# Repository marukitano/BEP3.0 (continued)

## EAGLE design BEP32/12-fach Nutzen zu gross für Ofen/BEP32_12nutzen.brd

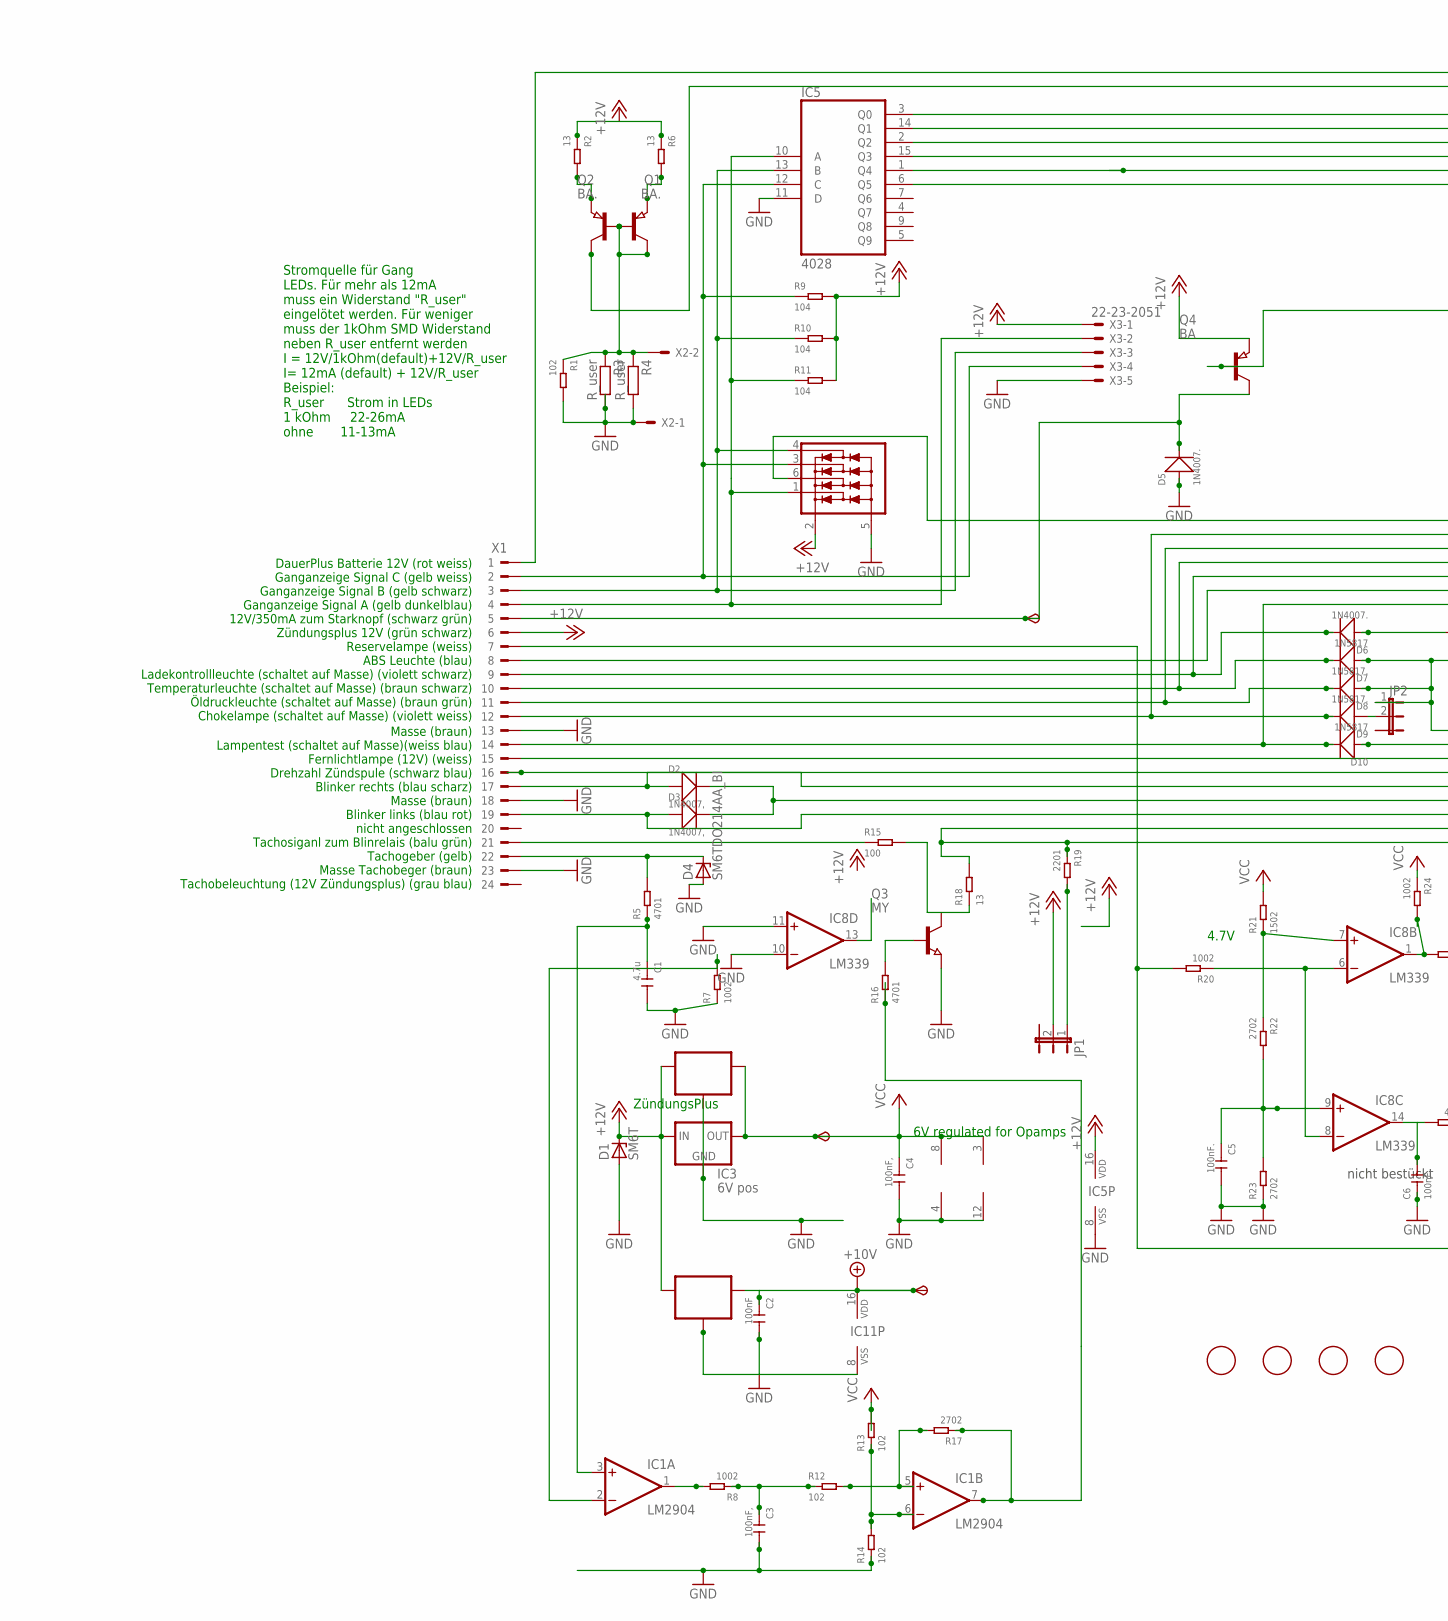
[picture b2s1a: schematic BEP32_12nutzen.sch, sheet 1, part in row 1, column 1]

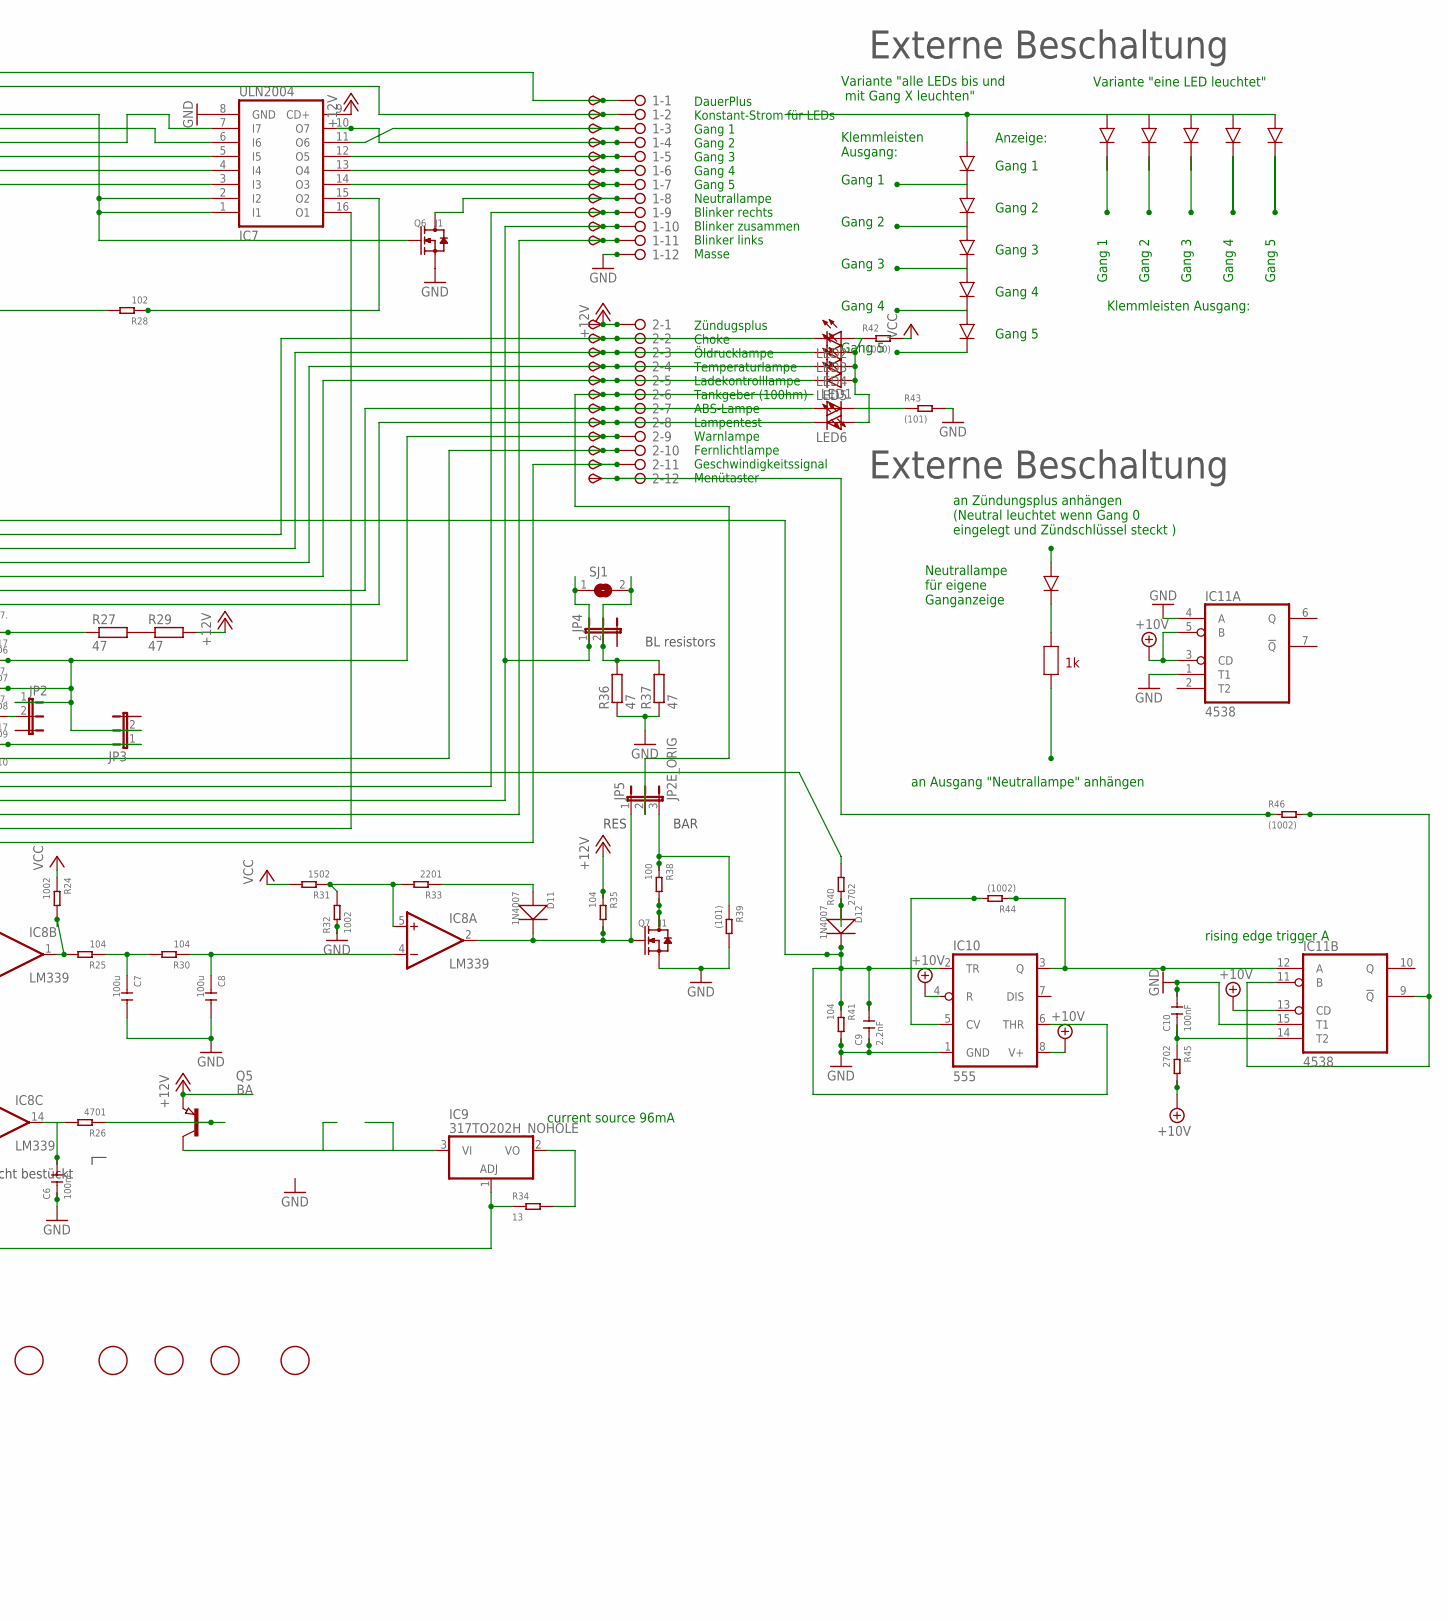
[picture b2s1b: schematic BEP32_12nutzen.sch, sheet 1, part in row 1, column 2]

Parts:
1, 2: 2081-1132; 12-PIN
6V, 10V: TPSB2.0; B2.0
C1: 4.7u; C0805
C2, C10: 100nF; C0805
C3, C4: 100nF,; C0805
C5, C6: 100nF.; C0805
C7, C8: 100u; C1206
C9: 2.2nF; C0805
D1: SM6T; DO214AA
D2, D3: 1N4007,; DO-214AC
D4: SM6TDO214AA_BI; DO214AA_BI
D5, D6: 1N4007.; DO-214AC
D7, D10: 1N5817; DO-214AC_SLIM
D8, D9: 1N5817.; DO-214AC_SLIM
D11, D12: 1N4007; DO-214AC
FID1, FID2, FID3, FID4, FID49, FID50, FID51, FID52: FIDUCIAL; FIDUCIAL_1MM
IC1: LM2904; SO08
IC2: 78L06; SOT89_ROUND
IC3: 6V pos; 78LXX
IC4: 78L10; SOT89_ROUND
IC5: 4028; SO16
IC6: NUP4304SOT457_R; SOT457R_PHILIPS
IC7: ULN2004; SO16
IC8: LM339; SO14
IC9: 317TO202H_NOHOLE; TO220H_NOHOLE
IC10: 555; SO08
IC11: 4538; SO16
JP1, JP2, JP3, JP4: JP2EJP2_SMALLPADS; JP2_SMALLPADS
JP5: JP2E_ORIG; JP2_ORIG_SMALLPADS
LED1, LED2, LED3, LED4, LED5, LED6: LEDLD260; LD260
Q1, Q2: BA.; SOT89
Q3: MY; SOT89
Q4, Q5: BA; SOT89
Q6, Q7: J1; SOT-23
R1, R12, R13, R14, R28: 102; R0805
R2, R6, R18, R34: 13; R1206
R3, R4: R_user; R0805
R5, R16, R26: 4701; R0805
R7, R8, R20, R24, R32: 1002; R0805
R9, R10, R11, R25, R30, R35, R41: 104; R0805
R15, R38: 100; R0805
R17, R22, R23, R40, R45: 2702; R0805
R19, R33: 2201; R0805
R21, R31: 1502; R0805
R27, R29, R36, R37: 47; V235/17_1MM
R39, R43: (101); R0805
R42: (1000); R0805
R44, R46: (1002); R0805
SJ1: SJ
START: TPSB2.0; B2.0
TP1, TP2, TP3, TP4, TP5, TP6, TP7, TP8, TP9, TP10, TP11, TP12, TP13, TP16, TP17, TP18, TP19, TP21, TP22, TP23, TP25, TP26: TPSB2.0; B2.0
TP24: TPSB1,27; B1,27
X1: CON_BMWV2; 24-PIN_V2
X2: 22-23-2021
X3: 22-23-2051

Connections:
+10V: 10V.TP, C2.1, IC4.1 (OUT), IC10.4 (R), IC10.8 (V+), IC11.3 (CD), IC11.5 (B), IC11.13 (CD), IC11.16 (VDD), R45.2; also elsewhere on the board
+12V: 2.1, D1.C, IC2.3 (IN), IC3.IN, IC4.3 (IN), IC5.16 (VDD), IC6.2 (V+), IC7.9 (CD+), JP1.2, Q4.3 (E), Q5.3 (E), R2.1, R6.1, R9.2, R10.2, R11.2, R29.2, R35.1, TP12.TP, X1.6, X3.1; also elsewhere on the board
+12V1: IC1.7 (OUT), R16.1, R17.1
GND: 1.12, C1.2, C2.2, C3.2, C4.2, C5.2, C6.1, C7.2, C8.2, C9.1, C10.2, D1.A, D4.A, D5.1 (+), IC1.4 (V-), IC2.2 (GND), IC2.2@1 (GND), IC3.GND, IC4.2 (GND), IC4.2@1 (GND), IC5.8 (VSS), IC5.11 (D), IC6.5 (V-), IC7.8 (GND), IC8.10 (-IN), IC8.11 (+IN), IC8.12 (GND), IC10.1 (GND), IC11.1 (T1), IC11.4 (A), IC11.8 (VSS), IC11.15 (T1), Q3.3 (E), Q6.2 (S), Q7.2 (S), R1.2, R3.2, R4.2, R7.1, R14.1, R23.1, R32.1, R36.1, R37.1, R39.2, R41.2, R43.2, X1.13, X1.18, X1.23, X2.1, X3.5; also elsewhere on the board
unnamed: 2.9, D7.1 (+), D8.1 (+), JP2.1, JP3.2, TP24.TP
unnamed: IC5.10 (A), IC6.1 (D1), R11.1, X1.4, X3.2
unnamed: IC5.13 (B), IC6.4 (D4), R10.1, X1.3, X3.3
unnamed: 2.7, LED1.A, TP22.TP, X1.8
unnamed: Q1.3 (E), R2.2
unnamed: D11.2 (-), IC8.2 (OUT), JP5.1, Q7.1 (G), R35.2
unnamed: IC1.2 (-IN), R7.2
unnamed: R27.2, R29.1
unnamed: Q2.3 (E), R6.2
unnamed: D5.2 (-), Q4.2 (C), START.TP, X1.5
unnamed: 2.2, D9.2 (-), LED2.K (C), TP16.TP, X1.12
unnamed: 2.3, D8.2 (-), LED3.K (C), TP17.TP, X1.11
unnamed: 2.4, D7.2 (-), LED4.K (C), TP18.TP, X1.10
unnamed: IC9.3 (VI), Q5.2 (C)
unnamed: IC8.6 (-IN), IC8.8 (-IN), R20.1
unnamed: IC5.12 (C), IC6.3 (D3), R9.1, X1.2, X3.4
unnamed: IC5.15 (Q3), IC7.5 (I5)
unnamed: 2.8, D10.2 (-), LED6.K (C), TP23.TP, X1.14
unnamed: 1.9, D2.1 (+), TP9.TP, X1.17
unnamed: 1.11, D3.1 (+), TP11.TP, X1.19
unnamed: IC11.9 (!Q), IC11.11 (B), R46.2
unnamed: D4.C, R5.2, X1.22
unnamed: C1.1, IC1.3 (+IN), R5.1
unnamed: 1.6, IC7.13 (O4), TP6.TP
unnamed: 1.7, IC7.14 (O3), TP7.TP
unnamed: 2.11, IC7.16 (O1), R18.2, R19.1, TP26.TP
unnamed: 2.6, JP5.2, TP21.TP
unnamed: JP1.1, R19.2
unnamed: C5.1, IC8.9 (+IN), R22.2, R23.2
unnamed: C6.2, IC8.14 (OUT), R26.2
unnamed: C9.2, D12.2 (-), IC6.6 (D2), IC10.2 (TR), IC10.6 (THR), R41.1
unnamed: LED1.K (C), R43.1
unnamed: IC9.1 (ADJ), R20.2, R34.1, X1.7
unnamed: Q5.1 (B), R26.1
unnamed: IC5.2 (Q2), IC7.7 (I7)
unnamed: 1.3, IC7.11 (O6), TP3.TP
unnamed: 1.5, IC7.12 (O5), TP5.TP
unnamed: LED2.A, LED3.A, LED4.A, LED5.A, LED6.A, R42.1
unnamed: R40.2, X1.16
unnamed: Q4.1 (B), R28.2
unnamed: IC5.3 (Q0), IC7.1 (I1), IC7.2 (I2), Q6.1 (G)
unnamed: C7.1, R25.1, R30.2
unnamed: C8.1, IC8.4 (-IN), R30.1
unnamed: IC8.5 (+IN), R31.1, R32.2, R33.2
unnamed: Q7.3 (D), R38.2
unnamed: D11.1 (+), R33.1
unnamed: IC5.1 (Q4), IC7.4 (I4)
unnamed: R15.1, X1.21
unnamed: 1.8, Q6.3 (D), TP8.TP
unnamed: 2.10, TP25.TP, X1.15
unnamed: D6.1 (+), R27.1
unnamed: 2.5, D6.2 (-), LED5.K (C), TP19.TP, X1.9
unnamed: IC5.14 (Q1), IC7.6 (I6)
unnamed: Q1.1 (B), Q2.1 (B), Q2.2 (C), R1.1, R3.1, R4.1, X2.2
unnamed: Q3.2 (C), R15.2, R18.1
unnamed: 1.2, Q1.2 (C), TP2.TP
unnamed: IC5.6 (Q5), IC7.3 (I3)
unnamed: IC9.2 (VO), R34.2
unnamed: IC10.5 (CV), R44.2
unnamed: 1.4, IC7.10 (O7), TP4.TP
unnamed: 1.1, TP1.TP, X1.1
unnamed: IC8.7 (+IN), R21.1, R22.1
unnamed: Q3.1 (B), R16.2
unnamed: IC10.3 (Q), IC11.12 (A), R44.1
unnamed: D12.1 (+), R40.1
unnamed: IC7.15 (O2), R28.1
unnamed: C10.1, IC11.14 (T2), R45.1
unnamed: 2.12, R46.1, TP13.TP
unnamed: IC1.1 (OUT), R8.2
unnamed: 1.10, D2.2 (-), D3.2 (-), JP4.1, SJ1.1, TP10.TP
unnamed: JP4.2, R36.2, R37.2, SJ1.2
unnamed: D9.1 (+), JP2.2
unnamed: C3.1, R8.1, R12.1
unnamed: IC1.5 (+IN), R12.2, R17.2
unnamed: D10.1 (+), JP3.1
unnamed: JP5.3, R38.1, R39.1
unnamed: IC1.6 (-IN), R13.1, R14.2
unnamed: IC8.1 (OUT), R24.2, R25.2
VCC: 6V.TP, C4.1, IC1.8 (V+), IC2.1 (OUT), IC3.OUT, IC8.3 (V+), R13.2, R21.2, R24.1, R31.2, R42.2; also elsewhere on the board

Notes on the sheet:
6V regulated for Opamps
current source 96mA
ZündungsPlus
Zündugsplus Choke Öldrucklampe Temperaturlampe Ladekontrolllampe Tankgeber (100hm) ABS-Lampe Lampentest Warnlampe Fernlichtlampe Geschwindigkeitssignal Menütaster
DauerPlus Konstant-Strom für LEDs Gang 1 Gang 2 Gang 3 Gang 4 Gang 5 Neutrallampe Blinker rechts Blinker zusammen Blinker links Masse
DauerPlus Batterie 12V (rot weiss) Ganganzeige Signal C (gelb weiss) Ganganzeige Signal B (gelb schwarz) Ganganzeige Signal A (gelb dunkelblau) 12V/350mA zum Starknopf (schwarz grün) Zündungsplus 12V (grün schwarz) Reservelampe (weiss) ABS Leuchte (blau) Ladekontrollleuchte (schaltet auf Masse) (vi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
Masse (braun) Lampentest (schaltet auf Masse)(weiss blau) Fernlichtlampe (12V) (weiss) Drehzahl Zündspule (schwarz blau) Blinker rechts (blau scharz) Masse (braun) Blinker links (blau rot) nicht angeschlossen Tachosiganl zum Blinrelais (balu grün) Tachogeber (gelb) Masse Tachobeger (braun) Tachobel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
4.7V
Stromquelle für Gang LEDs. Für mehr als 12mA muss ein Widerstand "R_user" eingelötet werden. Für weniger muss der 1kOhm SMD Widerstand neben R_user entfernt werden I = 12V/1kOhm(default)+12V/R_user I= 12mA (default) + 12V/R_user Beispiel: R_user Strom in LEDs 1 kOhm 22-26mA ohne 11-13mA
Gang 1
Gang 2
Gang 3
Gang 4
Gang 5
Variante "eine LED leuchtet"
Variante "alle LEDs bis und mit Gang X leuchten"
Klemmleisten Ausgang:
Klemmleisten Ausgang:
an Zündungsplus anhängen (Neutral leuchtet wenn Gang 0 eingelegt und Zündschlüssel steckt )
an Ausgang "Neutrallampe" anhängen
Neutrallampe für eigene Ganganzeige
Externe Beschaltung
Anzeige:
nicht bestückt
rising edge trigger A
BAR
RES
BL resistors

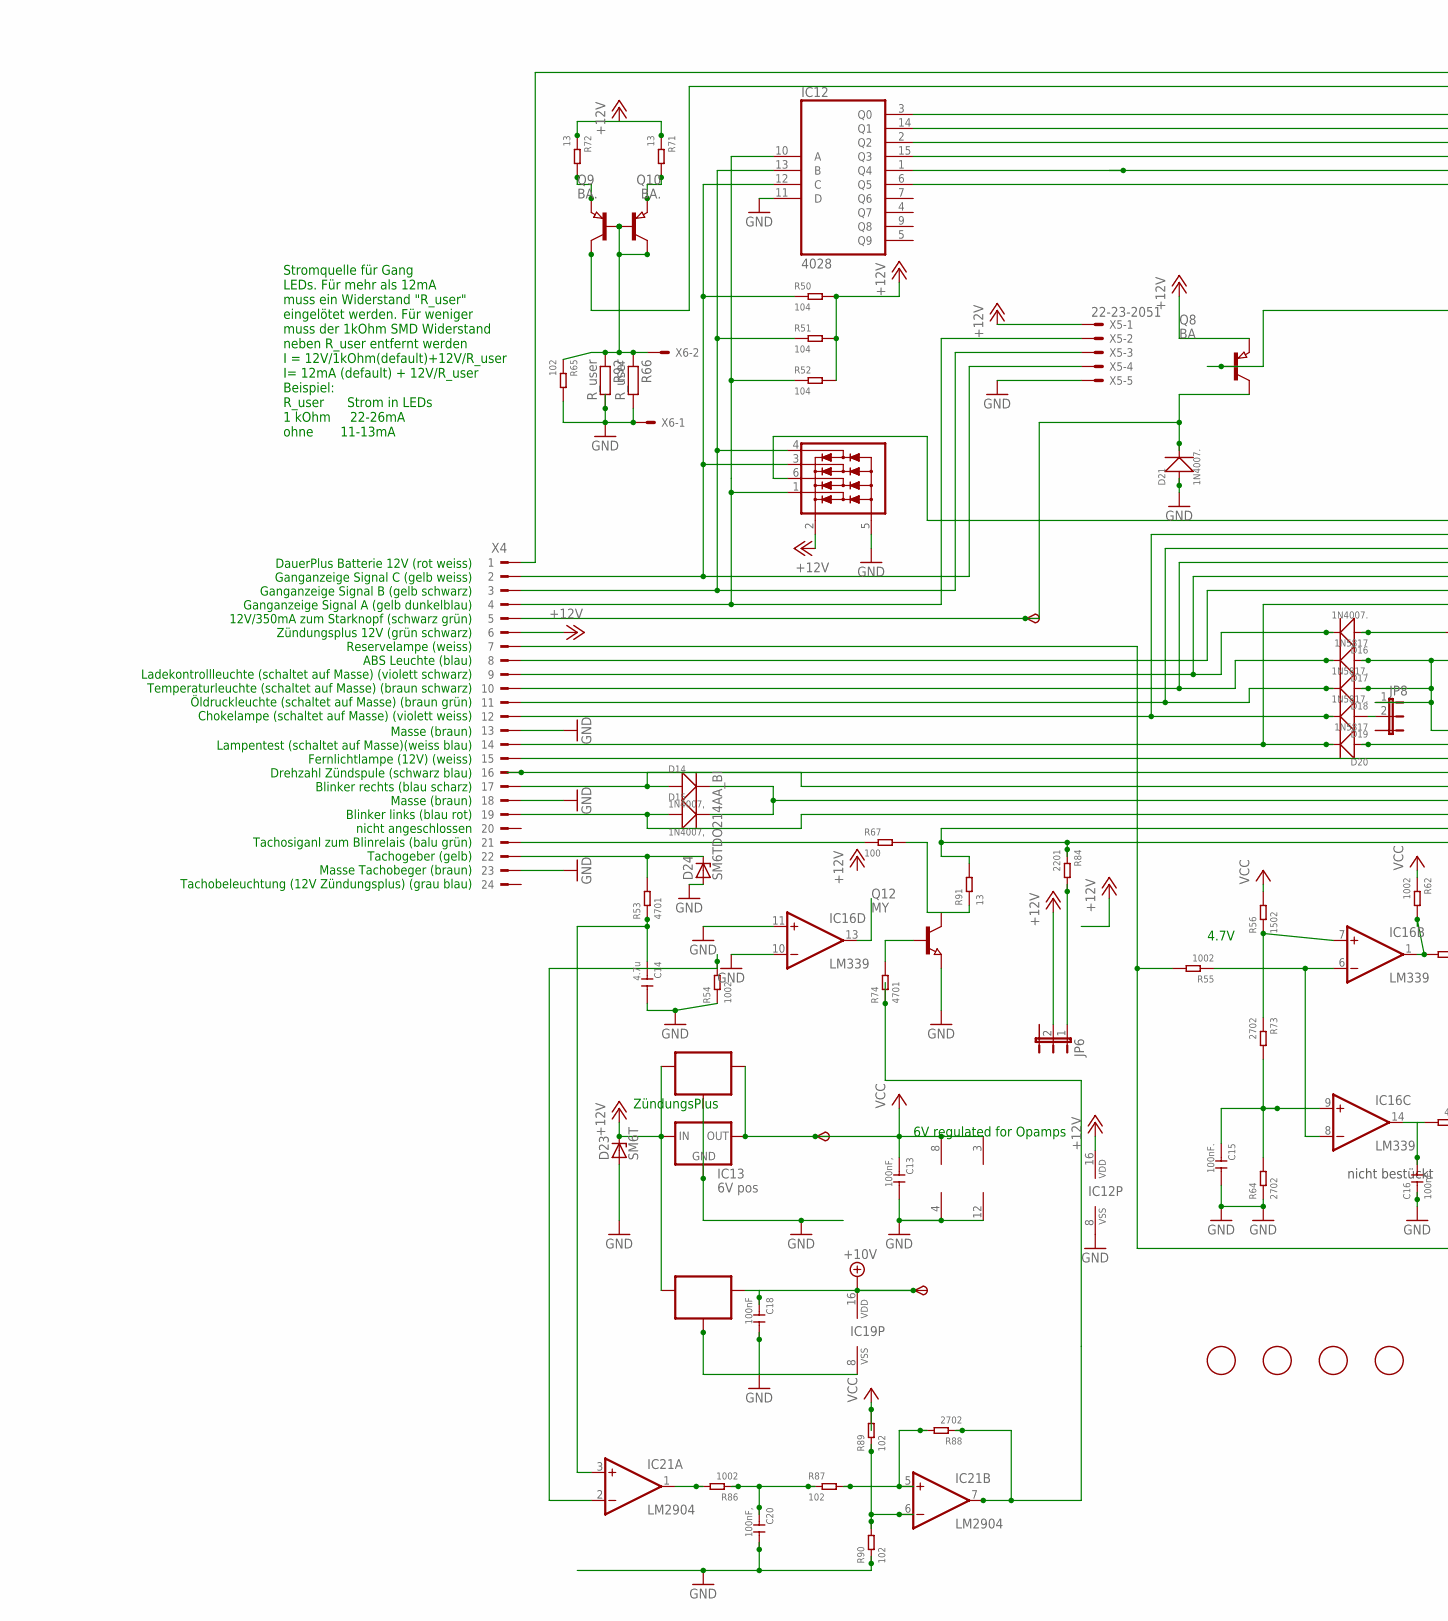
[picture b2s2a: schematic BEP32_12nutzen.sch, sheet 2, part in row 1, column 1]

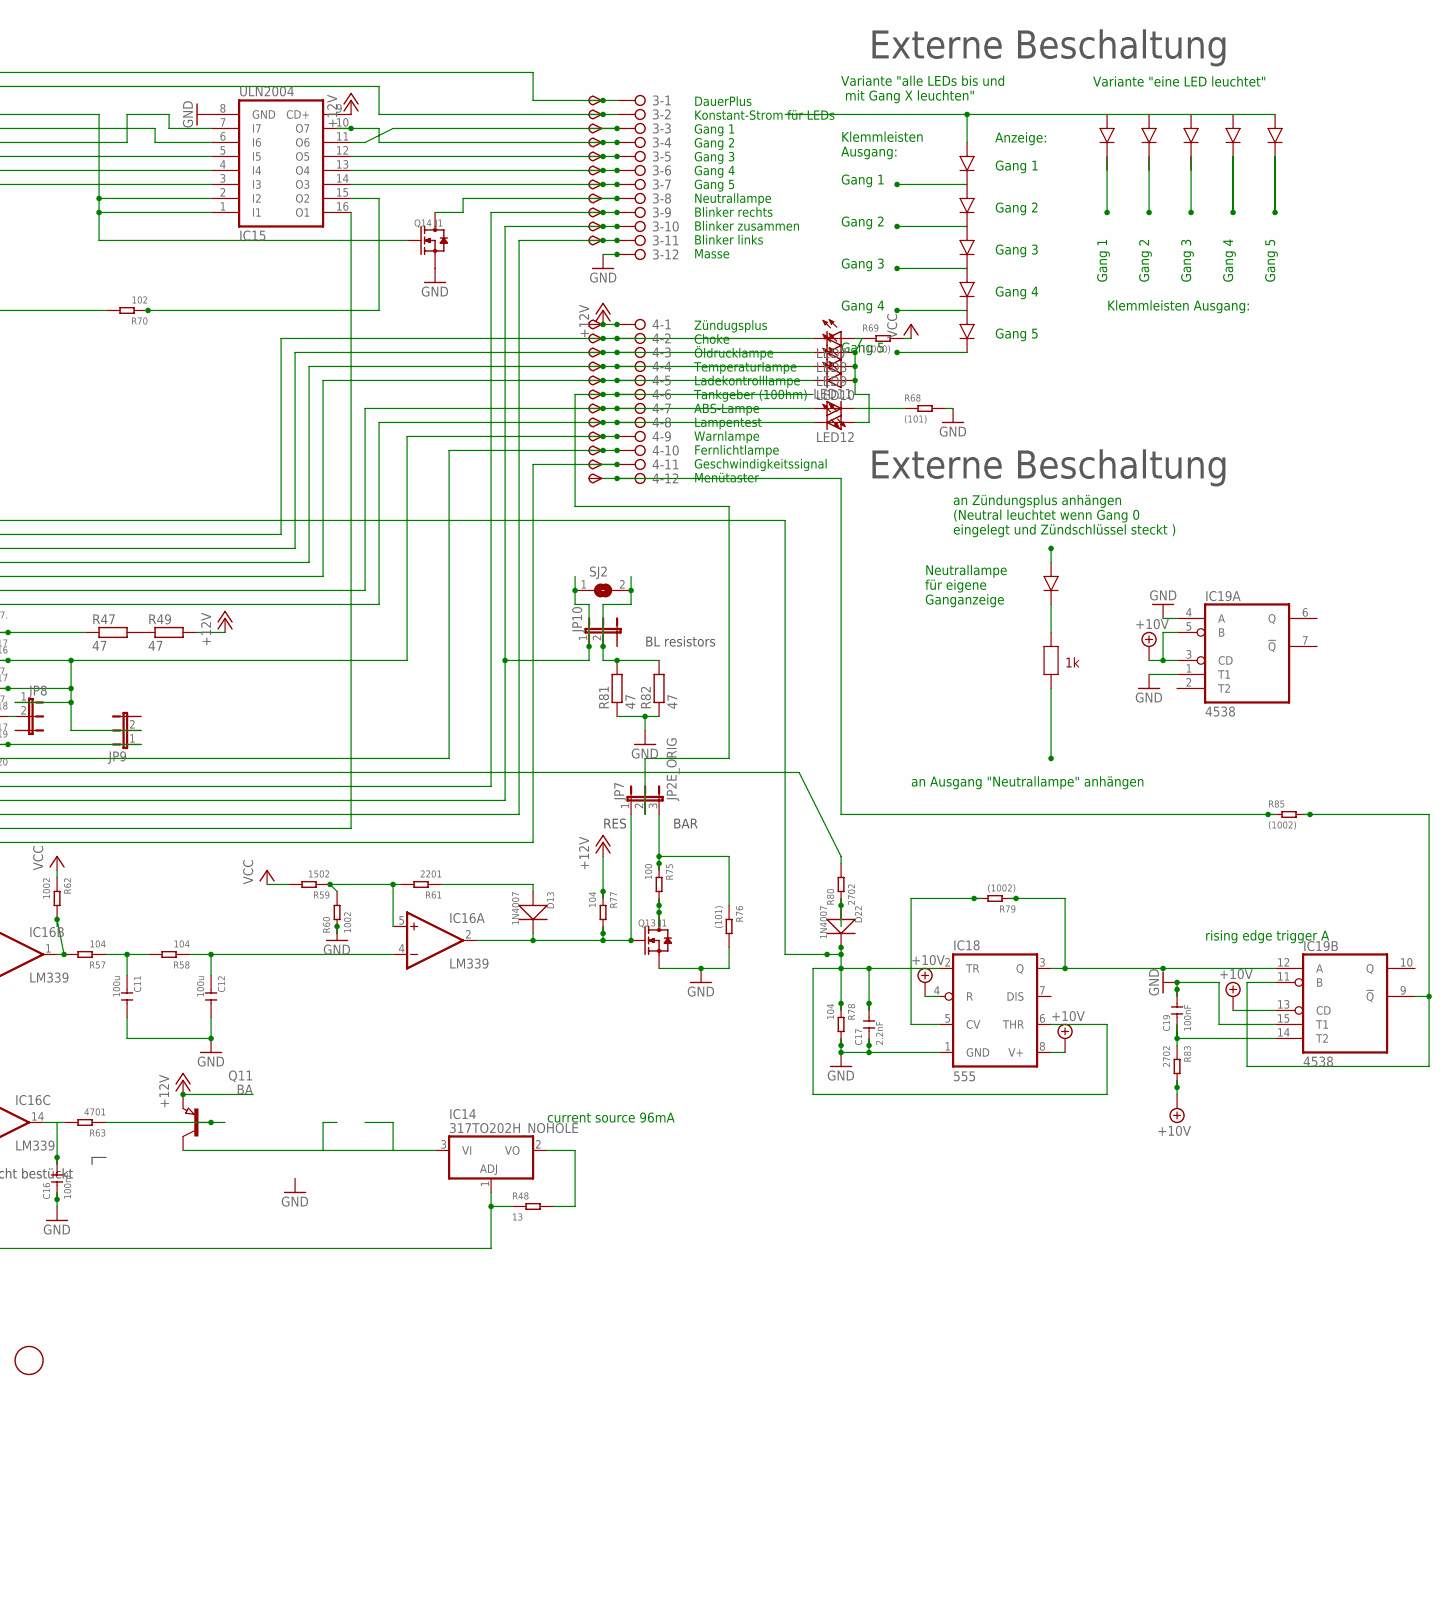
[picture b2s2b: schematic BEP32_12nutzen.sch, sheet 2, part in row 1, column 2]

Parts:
3, 4: 2081-1132; 12-PIN
6V1, 10V1: TPSB2.0; B2.0
C11, C12: 100u; C1206
C13, C20: 100nF,; C0805
C14: 4.7u; C0805
C15, C16: 100nF.; C0805
C17: 2.2nF; C0805
C18, C19: 100nF; C0805
D13, D22: 1N4007; DO-214AC
D14, D15: 1N4007,; DO-214AC
D16, D21: 1N4007.; DO-214AC
D17, D20: 1N5817; DO-214AC_SLIM
D18, D19: 1N5817.; DO-214AC_SLIM
D23: SM6T; DO214AA
D24: SM6TDO214AA_BI; DO214AA_BI
FID5, FID6, FID7, FID8: FIDUCIAL; FIDUCIAL_1MM
IC12: 4028; SO16
IC13: 6V pos; 78LXX
IC14: 317TO202H_NOHOLE; TO220H_NOHOLE
IC15: ULN2004; SO16
IC16: LM339; SO14
IC17: 78L06; SOT89_ROUND
IC18: 555; SO08
IC19: 4538; SO16
IC20: 78L10; SOT89_ROUND
IC21: LM2904; SO08
IC22: NUP4304SOT457_R; SOT457R_PHILIPS
JP6, JP8, JP9, JP10: JP2EJP2_SMALLPADS; JP2_SMALLPADS
JP7: JP2E_ORIG; JP2_ORIG_SMALLPADS
LED7, LED8, LED9, LED10, LED11, LED12: LEDLD260; LD260
Q8, Q11: BA; SOT89
Q9, Q10: BA.; SOT89
Q12: MY; SOT89
Q13, Q14: J1; SOT-23
R47, R49, R81, R82: 47; V235/17_1MM
R48, R71, R72, R91: 13; R1206
R50, R51, R52, R57, R58, R77, R78: 104; R0805
R53, R63, R74: 4701; R0805
R54, R55, R60, R62, R86: 1002; R0805
R56, R59: 1502; R0805
R61, R84: 2201; R0805
R64, R73, R80, R83, R88: 2702; R0805
R65, R70, R87, R89, R90: 102; R0805
R66, R92: R_user; R0805
R67, R75: 100; R0805
R68, R76: (101); R0805
R69: (1000); R0805
R79, R85: (1002); R0805
SJ2: SJ
START1: TPSB2.0; B2.0
TP14, TP15, TP20, TP27, TP28, TP29, TP30, TP31, TP32, TP33, TP34, TP35, TP36, TP37, TP38, TP39, TP40, TP41, TP43, TP44, TP45, TP46: TPSB2.0; B2.0
TP42: TPSB1,27; B1,27
X4: CON_BMWV2; 24-PIN_V2
X5: 22-23-2051
X6: 22-23-2021

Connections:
+10V: 10V1.TP, C18.1, IC18.4 (R), IC18.8 (V+), IC19.3 (CD), IC19.5 (B), IC19.13 (CD), IC19.16 (VDD), IC20.1 (OUT), R83.2; also elsewhere on the board
+12V: 4.1, D23.C, IC12.16 (VDD), IC13.IN, IC15.9 (CD+), IC17.3 (IN), IC20.3 (IN), IC22.2 (V+), JP6.2, Q8.3 (E), Q11.3 (E), R49.2, R50.2, R51.2, R52.2, R71.1, R72.1, R77.1, TP45.TP, X4.6, X5.1; also elsewhere on the board
+12V2: IC21.7 (OUT), R74.1, R88.1
GND: 3.12, C11.2, C12.2, C13.2, C14.2, C15.2, C16.1, C17.1, C18.2, C19.2, C20.2, D21.1 (+), D23.A, D24.A, IC12.8 (VSS), IC12.11 (D), IC13.GND, IC15.8 (GND), IC16.10 (-IN), IC16.11 (+IN), IC16.12 (GND), IC17.2 (GND), IC17.2@1 (GND), IC18.1 (GND), IC19.1 (T1), IC19.4 (A), IC19.8 (VSS), IC19.15 (T1), IC20.2 (GND), IC20.2@1 (GND), IC21.4 (V-), IC22.5 (V-), Q12.3 (E), Q13.2 (S), Q14.2 (S), R54.1, R60.1, R64.1, R65.2, R66.2, R68.2, R76.2, R78.2, R81.1, R82.1, R90.1, R92.2, X4.13, X4.18, X4.23, X5.5, X6.1; also elsewhere on the board
unnamed: R47.2, R49.1
unnamed: 4.9, D17.1 (+), D18.1 (+), JP8.1, JP9.2, TP42.TP
unnamed: IC12.10 (A), IC22.1 (D1), R52.1, X4.4, X5.2
unnamed: IC12.13 (B), IC22.4 (D4), R51.1, X4.3, X5.3
unnamed: D21.2 (-), Q8.2 (C), START1.TP, X4.5
unnamed: IC12.12 (C), IC22.3 (D3), R50.1, X4.2, X5.4
unnamed: 4.7, LED11.A, TP40.TP, X4.8
unnamed: 4.2, D19.2 (-), LED7.K (C), TP35.TP, X4.12
unnamed: 4.3, D18.2 (-), LED8.K (C), TP36.TP, X4.11
unnamed: 4.4, D17.2 (-), LED9.K (C), TP37.TP, X4.10
unnamed: 4.8, D20.2 (-), LED12.K (C), TP41.TP, X4.14
unnamed: 3.9, D14.1 (+), TP32.TP, X4.17
unnamed: 3.11, D15.1 (+), TP34.TP, X4.19
unnamed: D24.C, R53.2, X4.22
unnamed: C14.1, IC21.3 (+IN), R53.1
unnamed: 4.11, IC15.16 (O1), R84.1, R91.2, TP44.TP
unnamed: IC16.1 (OUT), R57.2, R62.2
unnamed: C11.1, R57.1, R58.2
unnamed: C12.1, IC16.4 (-IN), R58.1
unnamed: IC16.5 (+IN), R59.1, R60.2, R61.2
unnamed: D13.1 (+), R61.1
unnamed: C15.1, IC16.9 (+IN), R64.2, R73.2
unnamed: C16.2, IC16.14 (OUT), R63.2
unnamed: Q11.1 (B), R63.1
unnamed: IC12.2 (Q2), IC15.7 (I7)
unnamed: 3.5, IC15.12 (O5), TP28.TP
unnamed: IC12.1 (Q4), IC15.4 (I4)
unnamed: 3.8, Q14.3 (D), TP31.TP
unnamed: 4.10, TP43.TP, X4.15
unnamed: 4.5, D16.2 (-), LED10.K (C), TP38.TP, X4.9
unnamed: D16.1 (+), R47.1
unnamed: IC12.6 (Q5), IC15.3 (I3)
unnamed: 3.4, IC15.10 (O7), TP27.TP
unnamed: IC14.1 (ADJ), R48.1, R55.2, X4.7
unnamed: IC16.6 (-IN), IC16.8 (-IN), R55.1
unnamed: 3.2, Q10.2 (C), TP15.TP
unnamed: 3.1, TP14.TP, X4.1
unnamed: R80.2, X4.16
unnamed: IC12.15 (Q3), IC15.5 (I5)
unnamed: 3.6, IC15.13 (O4), TP29.TP
unnamed: 3.7, IC15.14 (O3), TP30.TP
unnamed: 4.6, JP7.2, TP39.TP
unnamed: LED11.K (C), R68.1
unnamed: LED7.A, LED8.A, LED9.A, LED10.A, LED12.A, R69.1
unnamed: Q8.1 (B), R70.2
unnamed: IC12.3 (Q0), IC15.1 (I1), IC15.2 (I2), Q14.1 (G)
unnamed: IC12.14 (Q1), IC15.6 (I6)
unnamed: 3.3, IC15.11 (O6), TP20.TP
unnamed: Q9.1 (B), Q9.2 (C), Q10.1 (B), R65.1, R66.1, R92.1, X6.2
unnamed: Q10.3 (E), R72.2
unnamed: Q9.3 (E), R71.2
unnamed: IC16.7 (+IN), R56.1, R73.1
unnamed: IC21.2 (-IN), R54.2
unnamed: Q12.1 (B), R74.2
unnamed: Q13.3 (D), R75.2
unnamed: IC14.2 (VO), R48.2
unnamed: IC14.3 (VI), Q11.2 (C)
unnamed: C17.2, D22.2 (-), IC18.2 (TR), IC18.6 (THR), IC22.6 (D2), R78.1
unnamed: IC18.5 (CV), R79.2
unnamed: IC18.3 (Q), IC19.12 (A), R79.1
unnamed: D22.1 (+), R80.1
unnamed: 3.10, D14.2 (-), D15.2 (-), JP10.1, SJ2.1, TP33.TP
unnamed: JP10.2, R81.2, R82.2, SJ2.2
unnamed: IC19.9 (!Q), IC19.11 (B), R85.2
unnamed: C19.1, IC19.14 (T2), R83.1
unnamed: JP6.1, R84.2
unnamed: IC15.15 (O2), R70.1
unnamed: 4.12, R85.1, TP46.TP
unnamed: D19.1 (+), JP8.2
unnamed: D13.2 (-), IC16.2 (OUT), JP7.1, Q13.1 (G), R77.2
unnamed: IC21.1 (OUT), R86.2
unnamed: C20.1, R86.1, R87.1
unnamed: IC21.5 (+IN), R87.2, R88.2
unnamed: IC21.6 (-IN), R89.1, R90.2
unnamed: D20.1 (+), JP9.1
unnamed: JP7.3, R75.1, R76.1
unnamed: R67.1, X4.21
unnamed: Q12.2 (C), R67.2, R91.1
VCC: 6V1.TP, C13.1, IC13.OUT, IC16.3 (V+), IC17.1 (OUT), IC21.8 (V+), R56.2, R59.2, R62.1, R69.2, R89.2; also elsewhere on the board

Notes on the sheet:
6V regulated for Opamps
current source 96mA
ZündungsPlus
Zündugsplus Choke Öldrucklampe Temperaturlampe Ladekontrolllampe Tankgeber (100hm) ABS-Lampe Lampentest Warnlampe Fernlichtlampe Geschwindigkeitssignal Menütaster
DauerPlus Konstant-Strom für LEDs Gang 1 Gang 2 Gang 3 Gang 4 Gang 5 Neutrallampe Blinker rechts Blinker zusammen Blinker links Masse
DauerPlus Batterie 12V (rot weiss) Ganganzeige Signal C (gelb weiss) Ganganzeige Signal B (gelb schwarz) Ganganzeige Signal A (gelb dunkelblau) 12V/350mA zum Starknopf (schwarz grün) Zündungsplus 12V (grün schwarz) Reservelampe (weiss) ABS Leuchte (blau) Ladekontrollleuchte (schaltet auf Masse) (vi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
Masse (braun) Lampentest (schaltet auf Masse)(weiss blau) Fernlichtlampe (12V) (weiss) Drehzahl Zündspule (schwarz blau) Blinker rechts (blau scharz) Masse (braun) Blinker links (blau rot) nicht angeschlossen Tachosiganl zum Blinrelais (balu grün) Tachogeber (gelb) Masse Tachobeger (braun) Tachobel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
4.7V
Stromquelle für Gang LEDs. Für mehr als 12mA muss ein Widerstand "R_user" eingelötet werden. Für weniger muss der 1kOhm SMD Widerstand neben R_user entfernt werden I = 12V/1kOhm(default)+12V/R_user I= 12mA (default) + 12V/R_user Beispiel: R_user Strom in LEDs 1 kOhm 22-26mA ohne 11-13mA
Gang 1
Gang 2
Gang 3
Gang 4
Gang 5
Variante "eine LED leuchtet"
Variante "alle LEDs bis und mit Gang X leuchten"
Klemmleisten Ausgang:
Klemmleisten Ausgang:
an Zündungsplus anhängen (Neutral leuchtet wenn Gang 0 eingelegt und Zündschlüssel steckt )
an Ausgang "Neutrallampe" anhängen
Neutrallampe für eigene Ganganzeige
Externe Beschaltung
Anzeige:
nicht bestückt
rising edge trigger A
BAR
RES
BL resistors
